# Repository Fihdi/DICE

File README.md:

# 6hp Sample and Hold / Random voltage generator

DICE contains a white noise generator, sample and hold and a comparator. This 6hp module creates various random voltages and gates, bringing variety and unpredictability into your patches. 

# Applications

- Random voltage generator
- Random gate generator
- Slew rate limiter
- Track and hold
- White noise generator
- Burst generator

# Jumpers
Two jumpers on the back of the module allow the COMP output to be configured:
- **Jumper in the ON position:** A trigger from TRG is always routed to the COMP output. This ensures an on-time trigger when using the COMP output as a burst generator.
- **Jumper in the OFF position**: The trigger from TRG is not routed to the COMP output.
- **Jumper in the AND position:** The COMP output is only active while a gate signal is present at the TRG input.
- **Jumper not in the AND position:** COMP outputs HIGH or LOW signals regardless of the TRG input.

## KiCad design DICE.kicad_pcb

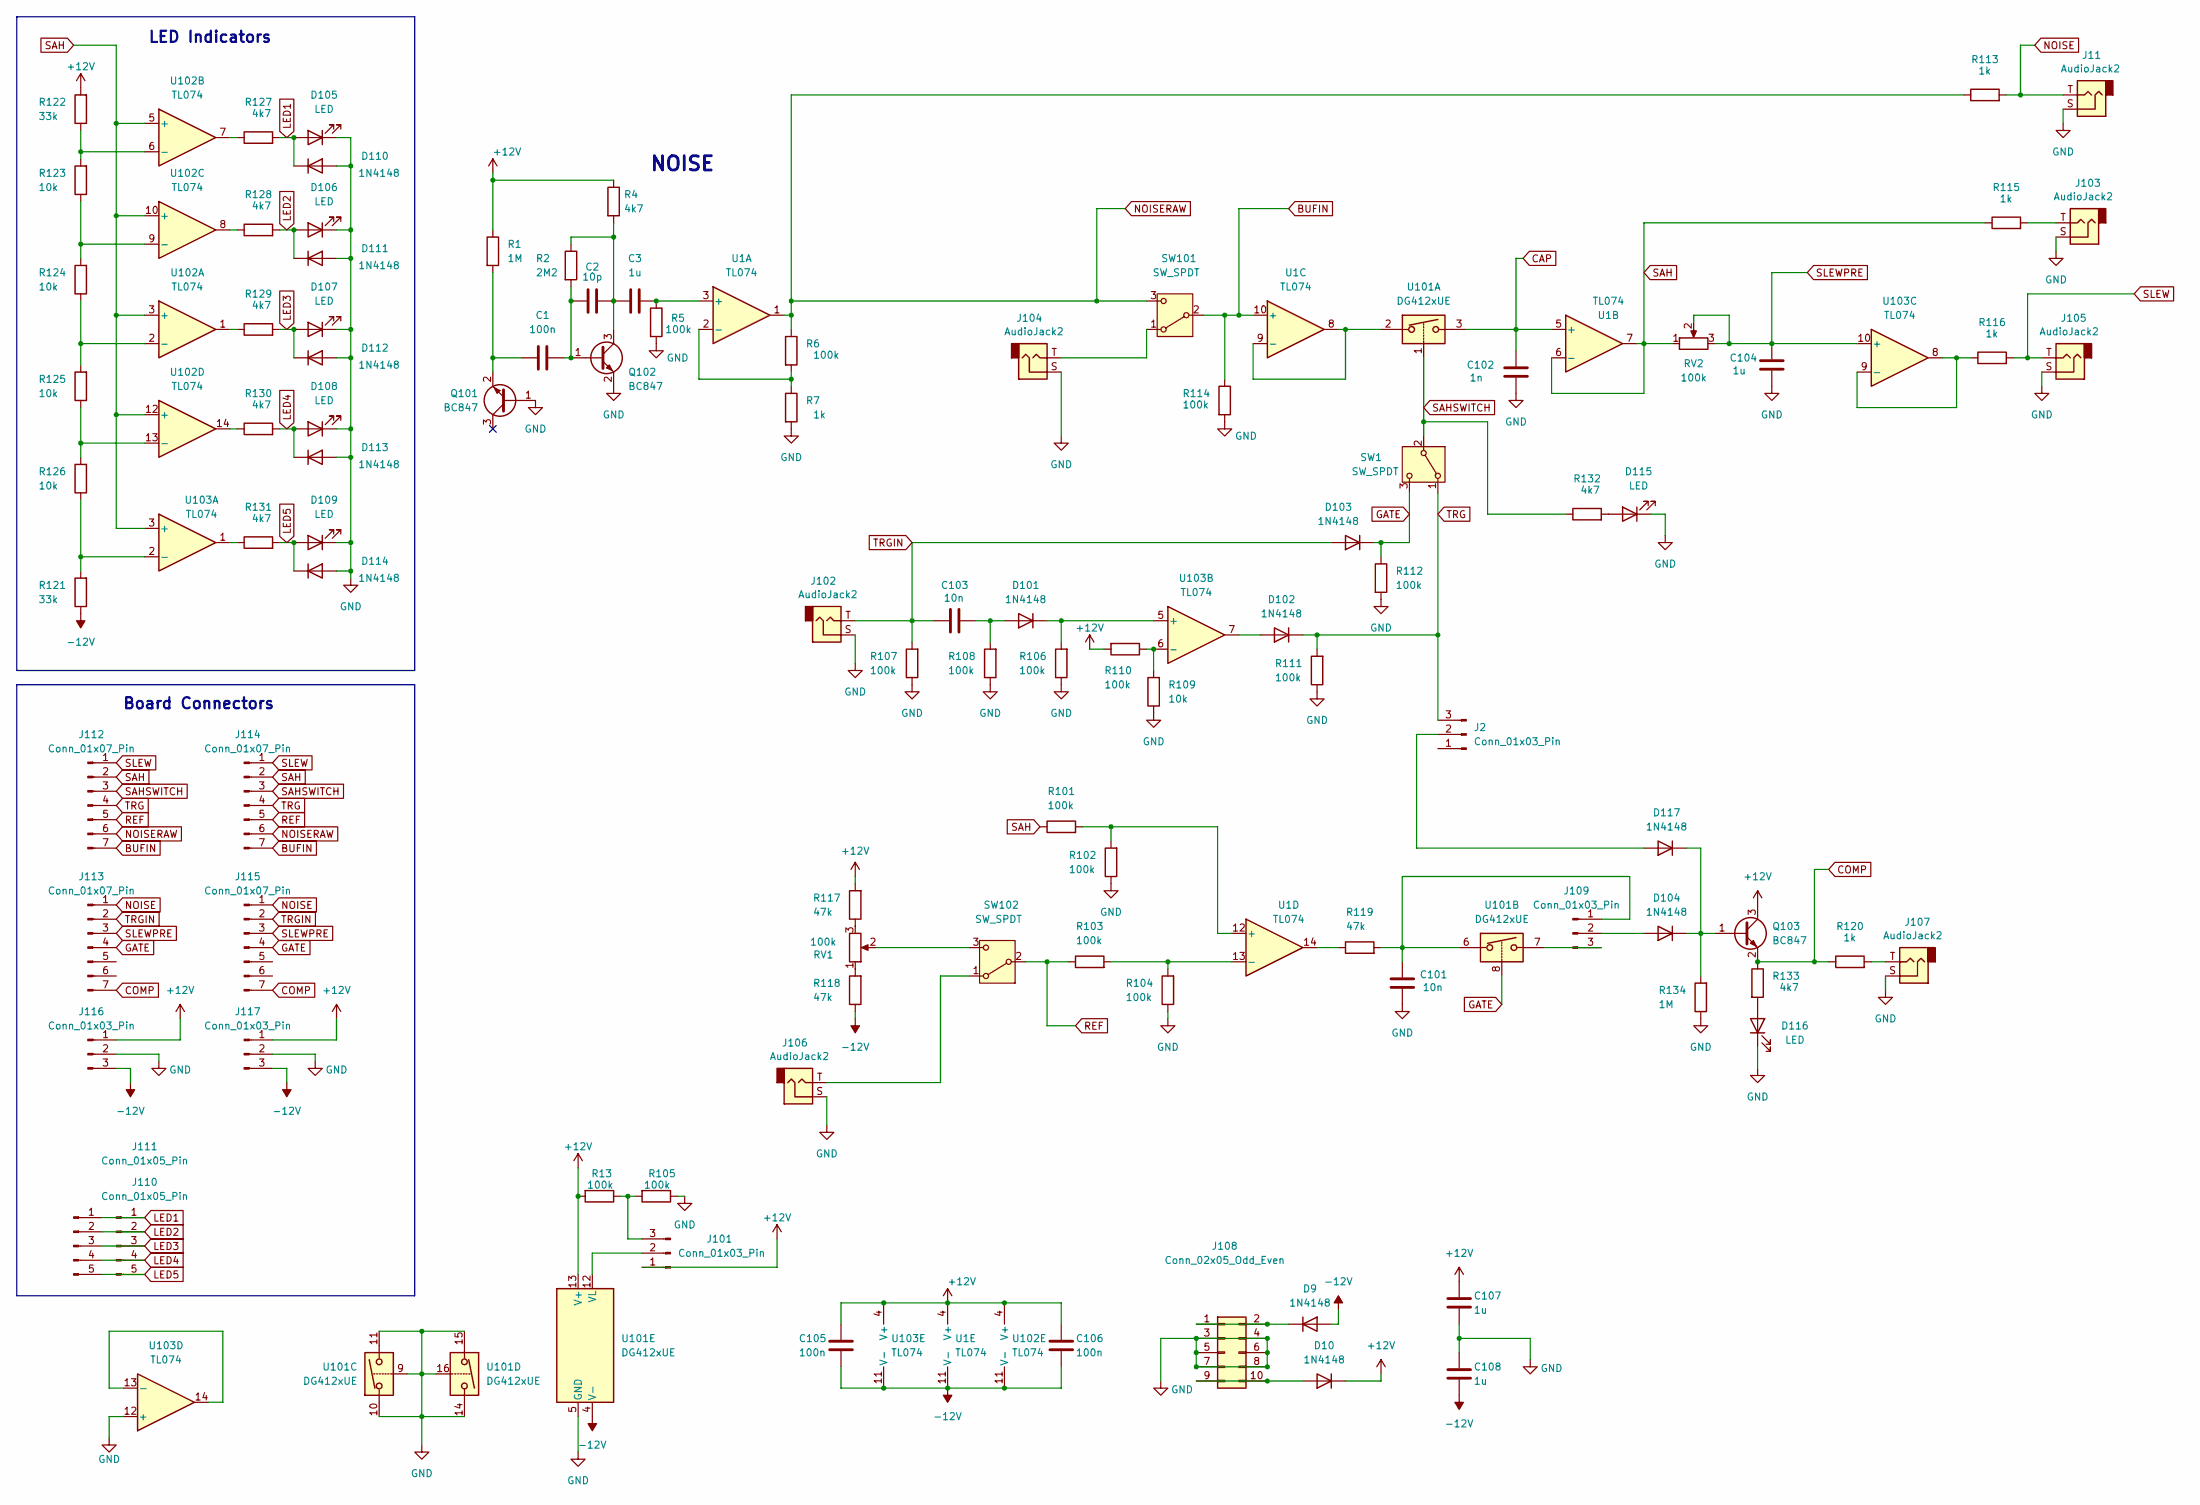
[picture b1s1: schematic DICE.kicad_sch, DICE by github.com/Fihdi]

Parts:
C1, C105, C106: 100n; C_1206_3216Metric
C2: 10p; C_1206_3216Metric
C3, C104, C107, C108: 1u; C_1206_3216Metric
C101, C103: 10n; C_1206_3216Metric
C102: 1n; C_1206_3216Metric
D9, D10, D101, D102, D103, D104, D110, D111, D112, D113, D114, D117: 1N4148; D_SOD-323_HandSoldering
D105, D106, D107, D108, D109, D115, D116: LED; LED_D3.0mm
J2, J101, J109, J116, J117: Conn_01x03_Pin; PinHeader_1x03_P2.54mm_Vertical
J11, J102, J103, J104, J105, J106, J107: AudioJack2; MonoTRS
J108: Conn_02x05_Odd_Even; IDC-Header_2x05_P2.54mm_Vertical
J110, J111: Conn_01x05_Pin; PinHeader_1x05_P2.54mm_Vertical
J112, J113, J114, J115: Conn_01x07_Pin; PinHeader_1x07_P2.54mm_Vertical
Q101, Q102, Q103: BC847; SOT-23
R1, R134: 1M; R_1206_3216Metric
R2: 2M2; R_1206_3216Metric
R4, R127, R128, R129, R130, R131, R132, R133: 4k7; R_1206_3216Metric
R5, R6, R13, R101, R102, R103, R104, R105, R106, R107, R108, R110, R111, R112, R114: 100k; R_1206_3216Metric
R7, R113, R115, R116, R120: 1k; R_1206_3216Metric
R109, R123, R124, R125, R126: 10k; R_1206_3216Metric
R117, R118, R119: 47k; R_1206_3216Metric
R121, R122: 33k; R_1206_3216Metric
RV1, RV2: 100k; Potentiometer_Alpha_RD901F-40-00D_Single_Vertical
SW1, SW101, SW102: SW_SPDT; Switch
U1, U102, U103: TL074; SOIC-14_3.9x8.7mm_P1.27mm
U101: DG412xUE; TSSOP-16_4.4x5mm_P0.65mm

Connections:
+12V: C105.1, C106.2, C107.2, D10.1 (K), J101.1, J116.1, J117.1, Q103.3 (C), R1.1, R4.1, R13.2, R110.2, R117.2, R122.2, U1.4 (V+), U101.13 (V+), U102.4 (V+), U103.4 (V+)
-12V: C105.2, C106.1, C108.1, D9.2 (A), J116.3, J117.3, R118.1, R121.1, U1.11 (V-), U101.4 (V-), U102.11 (V-), U103.11 (V-)
BUFIN: J112.7, J114.7, R114.1, SW101.2 (B), U1.10 (+)
CAP: C102.2, U1.5 (+), U101.3
COMP: J113.7, J115.7, Q103.2 (E), R120.1, R133.1
GATE: D103.1 (K), J113.4, J115.4, R112.1, SW1.3 (C), U101.8
GND: C101.1, C102.1, C104.1, C107.1, C108.2, D105.1 (K), D106.1 (K), D107.1 (K), D108.1 (K), D109.1 (K), D110.2 (A), D111.2 (A), D112.2 (A), D113.2 (A), D114.2 (A), D115.1 (K), D116.1 (K), J11.S, J102.S, J103.S, J104.S, J105.S, J106.S, J107.S, J108.3, J108.4, J108.5, J108.6, J108.7, J108.8, J116.2, J117.2, Q101.1 (B), Q102.2 (E), R5.2, R7.2, R102.1, R104.1, R105.1, R106.1, R107.1, R108.1, R109.1, R111.1, R112.2, R114.2, R134.1, U101.5 (GND), U101.9, U101.10, U101.11, U101.14, U101.15, U101.16, U103.12 (+)
LED1: D105.2 (A), D110.1 (K), J110.1, J111.1, R127.2
LED2: D106.2 (A), D111.1 (K), J110.2, J111.2, R128.2
LED3: D107.2 (A), D112.1 (K), J110.3, J111.3, R129.2
LED4: D108.2 (A), D113.1 (K), J110.4, J111.4, R130.2
LED5: D109.2 (A), D114.1 (K), J110.5, J111.5, R131.2
NOISE: J11.T, J113.1, J115.1, R113.2
NOISERAW: J112.6, J114.6, R6.1, R113.1, SW101.3 (C), U1.1
unnamed: D9.1 (K), J108.1, J108.2
unnamed: D10.2 (A), J108.9, J108.10
unnamed: C103.2, D101.2 (A), R108.2
unnamed: D101.1 (K), R106.2, U103.5 (+)
unnamed: D102.2 (A), U103.7
unnamed: D104.2 (A), J109.2
unnamed: D104.1 (K), D117.1 (K), Q103.1 (B), R134.2
unnamed: D115.2 (A), R132.2
unnamed: D116.2 (A), R133.2
unnamed: D117.2 (A), J2.2
unnamed: J101.2, U101.12 (VL)
unnamed: J101.3, R13.1, R105.2
unnamed: J103.T, R115.2
unnamed: J107.T, R120.2
unnamed: C101.2, J109.1, R119.2, U101.6
unnamed: J109.3, U101.7
unnamed: C1.1, Q101.2 (E), R1.2
unnamed: C1.2, C2.1, Q102.1 (B), R2.2
unnamed: C2.2, C3.1, Q102.3 (C), R2.1, R4.2
unnamed: R117.1, RV1.3
unnamed: R118.2, RV1.1
unnamed: R119.1, U1.14
unnamed: R127.1, U102.7
unnamed: R128.1, U102.8
unnamed: R129.1, U102.1
unnamed: R130.1, U102.14
unnamed: R131.1, U103.1
unnamed: J104.T, SW101.1 (A)
unnamed: J106.T, SW102.1 (A)
unnamed: RV1.2, SW102.3 (C)
unnamed: C3.2, R5.1, U1.3 (+)
unnamed: R6.2, R7.1, U1.2 (-)
unnamed: U1.8, U1.9 (-), U101.2
unnamed: R101.2, R102.2, U1.12 (+)
unnamed: R103.2, R104.2, U1.13 (-)
unnamed: R124.1, R125.2, U102.2 (-)
unnamed: R122.1, R123.2, U102.6 (-)
unnamed: R123.1, R124.2, U102.9 (-)
unnamed: R125.1, R126.2, U102.13 (-)
unnamed: R121.2, R126.1, U103.2 (-)
unnamed: R109.2, R110.1, U103.6 (-)
unnamed: R116.1, U103.8, U103.9 (-)
unnamed: U103.13 (-), U103.14
REF: J112.5, J114.5, R103.1, SW102.2 (B)
SAH: J112.2, J114.2, R101.1, R115.1, RV2.1, U1.6 (-), U1.7, U102.3 (+), U102.5 (+), U102.10 (+), U102.12 (+), U103.3 (+)
SAHSWITCH: J112.3, J114.3, R132.1, SW1.2 (B), U101.1
SLEW: J105.T, J112.1, J114.1, R116.2
SLEWPRE: C104.2, J113.3, J115.3, RV2.2, RV2.3, U103.10 (+)
TRG: D102.1 (K), J2.3, J112.4, J114.4, R111.2, SW1.1 (A)
TRGIN: C103.1, D103.2 (A), J102.T, J113.2, J115.2, R107.2

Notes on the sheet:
NOISE
LED Indicators
Board Connectors

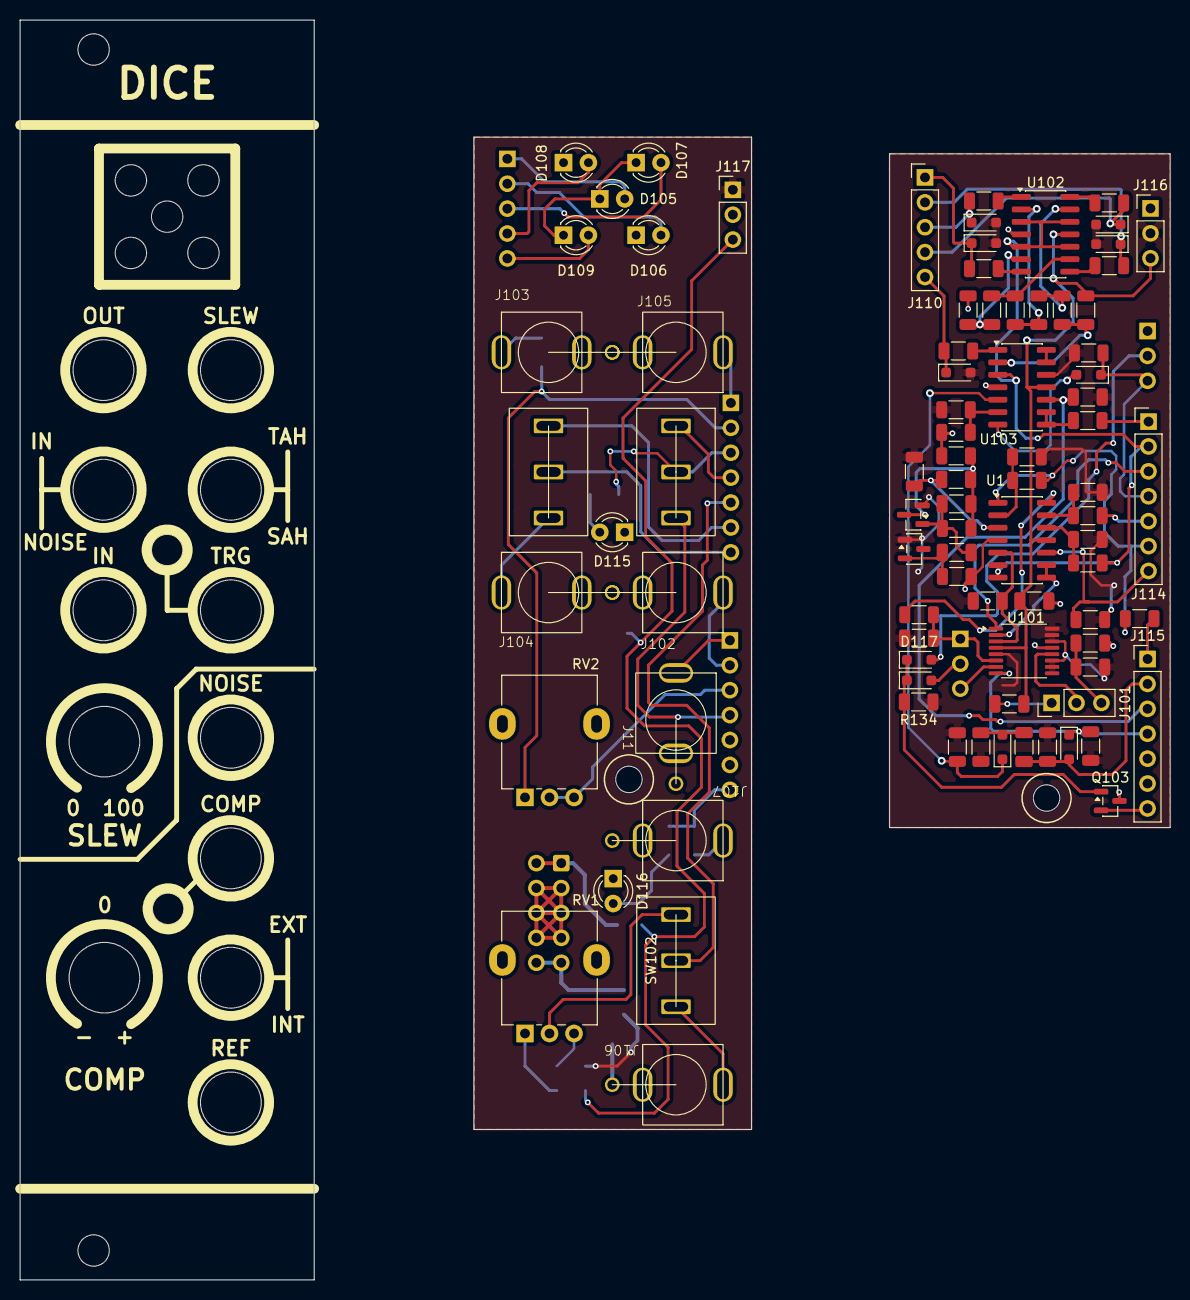
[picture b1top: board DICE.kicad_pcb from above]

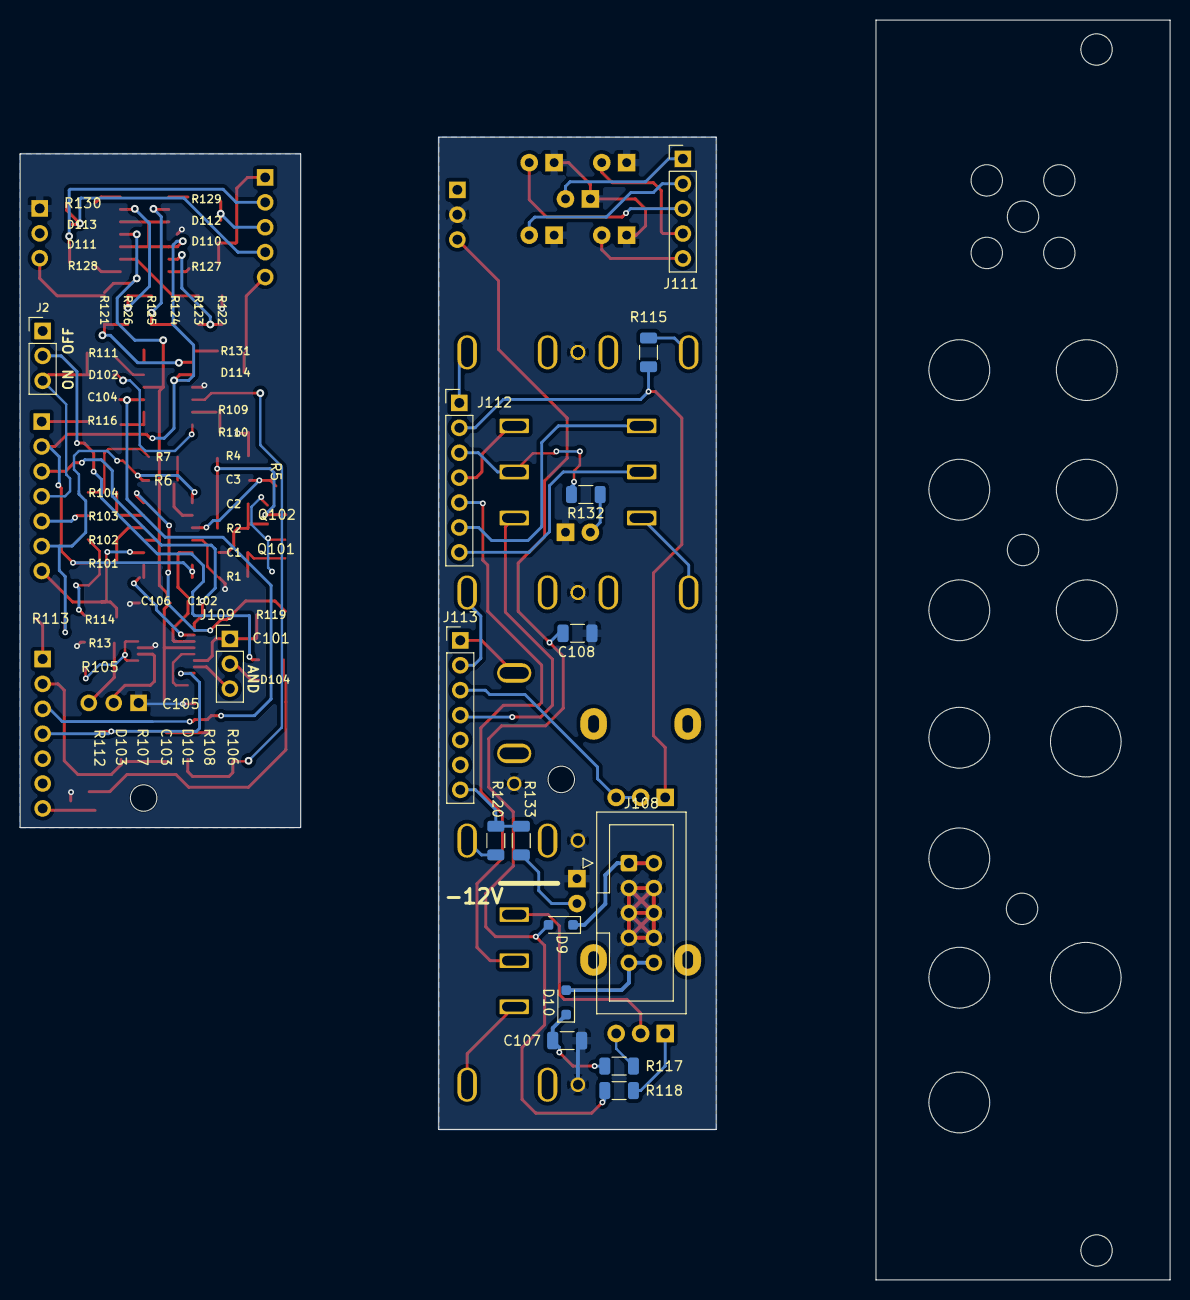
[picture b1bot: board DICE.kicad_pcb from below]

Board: 2 copper layers, 117.3 x 128.5 mm, 102 parts (16 on the bottom side), 64 nets.

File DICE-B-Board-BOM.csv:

"Reference","Value","Footprint","Qty"
"C1,C105,C106","100n","Capacitor_SMD:C_1206_3216Metric","3"
"C2","10p","Capacitor_SMD:C_1206_3216Metric","1"
"C3,C104","1u","Capacitor_SMD:C_1206_3216Metric","2"
"C101,C103","10n","Capacitor_SMD:C_1206_3216Metric","2"
"C102","1n","Capacitor_SMD:C_1206_3216Metric","1"
"D101,D102,D103,D104,D110,D111,D112,D113,D114,D117","1N4148","Diode_SMD:D_SOD-323_HandSoldering","10"
"J2,J101,J109,J116","Conn_01x03_Pin","Connector_PinHeader_2.54mm:PinHeader_1x03_P2.54mm_Vertical","4"
"J110","Conn_01x05_Pin","Connector_PinHeader_2.54mm:PinHeader_1x05_P2.54mm_Vertical","1"
"J114,J115","Conn_01x07_Pin","Connector_PinHeader_2.54mm:PinHeader_1x07_P2.54mm_Vertical","2"
"Q101,Q102,Q103","BC847","Package_TO_SOT_SMD:SOT-23","3"
"R1,R134","1M","Resistor_SMD:R_1206_3216Metric","2"
"R2","2M2","Resistor_SMD:R_1206_3216Metric","1"
"R4,R127,R128,R129,R130,R131","4k7","Resistor_SMD:R_1206_3216Metric","6"
"R5,R6,R13,R101,R102,R103,R104,R105,R106,R107,R108,R110,R111,R112,R114","100k","Resistor_SMD:R_1206_3216Metric","15"
"R7,R113,R116","1k","Resistor_SMD:R_1206_3216Metric","3"
"R109,R123,R124,R125,R126","10k","Resistor_SMD:R_1206_3216Metric","5"
"R119","47k","Resistor_SMD:R_1206_3216Metric","1"
"R121,R122","33k","Resistor_SMD:R_1206_3216Metric","2"
"U1,U102,U103","TL074","Package_SO:SOIC-14_3.9x8.7mm_P1.27mm","3"
"U101","DG412xUE","Package_SO:TSSOP-16_4.4x5mm_P0.65mm","1"
